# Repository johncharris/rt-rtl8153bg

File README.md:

# rt_rtl8156bg

RTL8156 Ethernet Controller

Created by John Harris <john@ziatech.net>

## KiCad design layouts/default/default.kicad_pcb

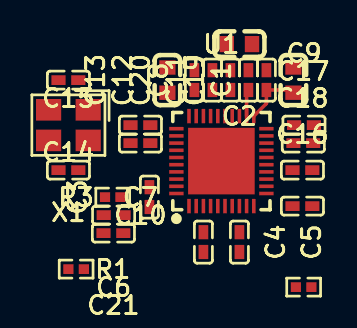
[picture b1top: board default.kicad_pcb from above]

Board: 2 copper layers, 26 parts (0 on the bottom side), 14 nets.

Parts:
C1, C2: 10µF ±20% 16V X5R; C0603
C3, C4, C5, C10, C11, C17, C18: 100nF ±10% 6.3V X7R; C0402
C6, C7, C8, C9, C12, C16, C19, C20, C21: 100nF ±10% 16V X7R; C0402
C13: 1µF ±10% 6.3V X7R; C0603
C14, C15: 18pF ±5% 50V C0G; C0402
R1: 10kΩ ±1% 62.5mW; R0402
R2, R3: 330Ω ±1% 62.5mW; R0402
U1: QFN-40_L5.0-W5.0-P0.40-BL-EP3.7
X1: CRYSTAL-SMD_4P-L3.2-W2.5-BL

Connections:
AVDD10: C3.1, C4.1, C5.1, U1.3, U1.8, U1.37
CKXTAL1: C14.1, U1.35, X1.1
CKXTAL2: C15.1, U1.36, X1.3
DVDD10: C10.1, U1.34
DVDD10_UPS: C11.1, U1.22
EESK_LED1_SPISCK: R3.1, U1.30
GND: C1.2, C2.2, C3.2, C4.2, C5.2, C6.2, C7.2, C8.2, C9.2, C10.2, C11.2, C12.2, C13.2, C14.2, C15.2, C16.2, C17.2, C18.2, C19.2, C20.2, C21.2, R1.2, U1.29, U1.41, X1.2, X1.4
LED0_SPICSB: R2.1, U1.32
REGOUT: C13.1, U1.28
RSET: R1.1, U1.38
U2VDD10: C17.1, U1.19
U3VDD10: C18.1, U1.14
power_3v3-VCC: C2.1, C6.1, C7.1, C8.1, C9.1, C12.1, C16.1, C21.1, U1.11, U1.20, U1.23, U1.26, U1.33, U1.39, U1.40
power_5v-VCC: C1.1, C19.1, C20.1, U1.21, U1.27

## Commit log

2025-09-08 Updated ato.yaml to resolve identifier issues.
2025-09-09 Renamed the module and adjusted the layout.
